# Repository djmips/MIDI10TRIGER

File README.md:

# MIDI10TRIGER
MIDI 2 eleven triggers with clock and reset

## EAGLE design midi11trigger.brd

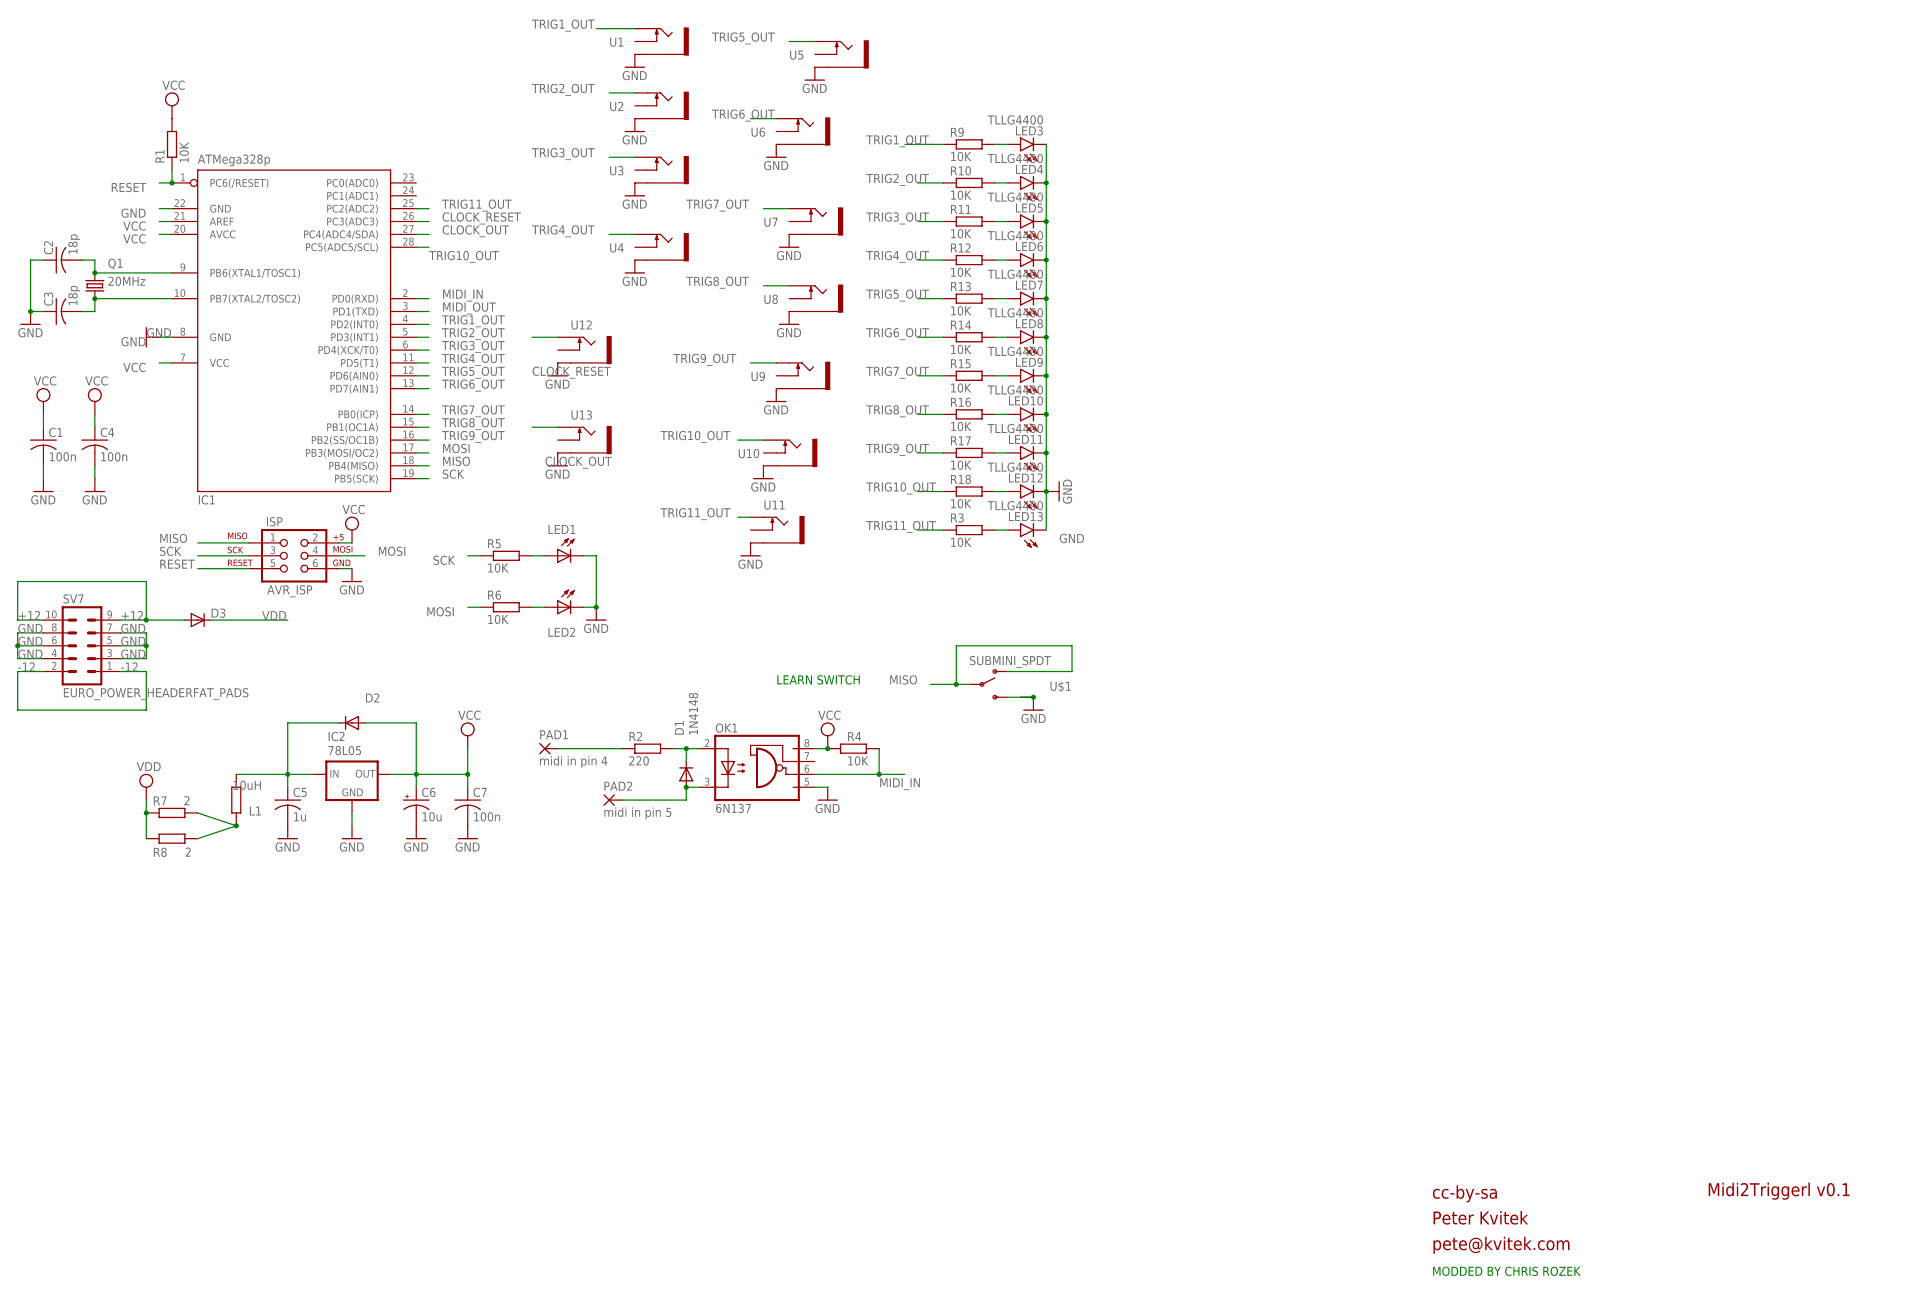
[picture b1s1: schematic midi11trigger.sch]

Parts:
C1, C4, C7: 100n; C025-025X050
C2, C3: 18p; C025-025X050
C5: 1u; C025-025X050
C6: 10u; E2,5-5
D1: 1N4148; DO35-7
D2, D3: SMALL_DIODEDO35-7; DO35-7
IC1: ATMega328p; DIL28-3
IC2: 78L05; 78LXX
ISP: AVR_ISP; 2X3
L1: 10uH; VERTICAL_RESISTOR
LED1, LED2: LED3MM
LED3, LED4, LED5, LED6, LED7, LED8, LED9, LED10, LED11, LED12, LED13: TLLG4400; LED3MM
OK1: 6N137; DIL08
PAD1: midi in pin 4; 2,54/1,1
PAD2: midi in pin 5; 2,54/1,1
Q1: 20MHz; HC49U-V
R1, R3, R4, R5, R6, R9, R10, R11, R12, R13, R14, R15, R16, R17, R18: 10K; VERTICAL_RESISTOR
R2: 220; VERTICAL_RESISTOR
R7, R8: 2; VERTICAL_RESISTOR
SV7: EURO_POWER_HEADERFAT_PADS; EURO_PWR_HEADER_FAT
U1, U2, U3, U4, U5, U6, U7, U8, U9, U10, U11, U12, U13: THONKICONNNEW; WQP-PJ301M-12_JACK
U$1: SUBMINI_SPDT; SUBMINI_TOGGLE

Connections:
+12: D3.A, SV7.9, SV7.10
-12: SV7.1, SV7.2
CLOCK_OUT: IC1.27 (PC4(ADC4/SDA)), U13.P$1_TIP (TIP)
CLOCK_RESET: IC1.26 (PC3(ADC3)), U12.P$1_TIP (TIP)
GND: C1.2, C2.1, C3.1, C4.2, C5.2, C6.-, C7.2, IC1.8 (GND), IC1.22 (GND), IC2.GND, ISP.6, LED1.K (C), LED2.K (C), LED3.K (C), LED4.K (C), LED5.K (C), LED6.K (C), LED7.K (C), LED8.K (C), LED9.K (C), LED10.K (C), LED11.K (C), LED12.K (C), LED13.K (C), OK1.5 (GND), SV7.3, SV7.4, SV7.5, SV7.6, SV7.7, SV7.8, U1.P$3_SLEEVE (SLEEVE), U2.P$3_SLEEVE (SLEEVE), U3.P$3_SLEEVE (SLEEVE), U4.P$3_SLEEVE (SLEEVE), U5.P$3_SLEEVE (SLEEVE), U6.P$3_SLEEVE (SLEEVE), U7.P$3_SLEEVE (SLEEVE), U8.P$3_SLEEVE (SLEEVE), U9.P$3_SLEEVE (SLEEVE), U10.P$3_SLEEVE (SLEEVE), U11.P$3_SLEEVE (SLEEVE), U12.P$3_SLEEVE (SLEEVE), U13.P$3_SLEEVE (SLEEVE), U$1.3 (S)
MIDI_IN: IC1.2 (PD0(RXD)), OK1.6 (VO), R4.2
MIDI_OUT: IC1.3 (PD1(TXD))
MISO: IC1.18 (PB4(MISO)), ISP.1, U$1.1 (O), U$1.COM (COMMON)
MOSI: IC1.17 (PB3(MOSI/OC2)), ISP.4, R6.1
unnamed: L1.1, R7.2, R8.2
unnamed: D1.C, OK1.2 (A), R2.2
unnamed: LED13.A, R3.2
unnamed: LED1.A, R5.2
unnamed: LED2.A, R6.2
unnamed: LED3.A, R9.2
unnamed: LED4.A, R10.2
unnamed: LED5.A, R11.2
unnamed: LED6.A, R12.2
unnamed: LED7.A, R13.2
unnamed: LED8.A, R14.2
unnamed: LED9.A, R15.2
unnamed: LED10.A, R16.2
unnamed: LED11.A, R17.2
unnamed: LED12.A, R18.2
unnamed: PAD1.1, R2.1
unnamed: D1.A, OK1.3 (C), PAD2.1
unnamed: C3.2, IC1.10 (PB7(XTAL2/TOSC2)), Q1.1
unnamed: C2.2, IC1.9 (PB6(XTAL1/TOSC1)), Q1.2
RESET: IC1.1 (PC6(/RESET)), ISP.5, R1.1
SCK: IC1.19 (PB5(SCK)), ISP.3, R5.1
TRIG1_OUT: IC1.4 (PD2(INT0)), R9.1, U1.P$1_TIP (TIP)
TRIG2_OUT: IC1.5 (PD3(INT1)), R10.1, U2.P$1_TIP (TIP)
TRIG3_OUT: IC1.6 (PD4(XCK/T0)), R11.1, U3.P$1_TIP (TIP)
TRIG4_OUT: IC1.11 (PD5(T1)), R12.1, U4.P$1_TIP (TIP)
TRIG5_OUT: IC1.12 (PD6(AIN0)), R13.1, U5.P$1_TIP (TIP)
TRIG6_OUT: IC1.13 (PD7(AIN1)), R14.1, U6.P$1_TIP (TIP)
TRIG7_OUT: IC1.14 (PB0(ICP)), R15.1, U7.P$1_TIP (TIP)
TRIG8_OUT: IC1.15 (PB1(OC1A)), R16.1, U8.P$1_TIP (TIP)
TRIG9_OUT: IC1.16 (PB2(SS/OC1B)), R17.1, U9.P$1_TIP (TIP)
TRIG10_OUT: IC1.28 (PC5(ADC5/SCL)), R18.1, U10.P$1_TIP (TIP)
TRIG11_OUT: IC1.25 (PC2(ADC2)), R3.1, U11.P$1_TIP (TIP)
VCC: C1.1, C4.1, C6.+, C7.1, D2.A, IC1.7 (VCC), IC1.20 (AVCC), IC1.21 (AREF), IC2.OUT, ISP.2, OK1.8 (VCC), R1.2, R4.1
VDD: D3.C, R7.1, R8.1
VREG_IN: C5.1, D2.C, IC2.IN, L1.2

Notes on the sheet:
cc-by-sa
Peter Kvitek
pete@kvitek.com
Midi2Triggerl v0.1
LEARN SWITCH
MODDED BY CHRIS ROZEK

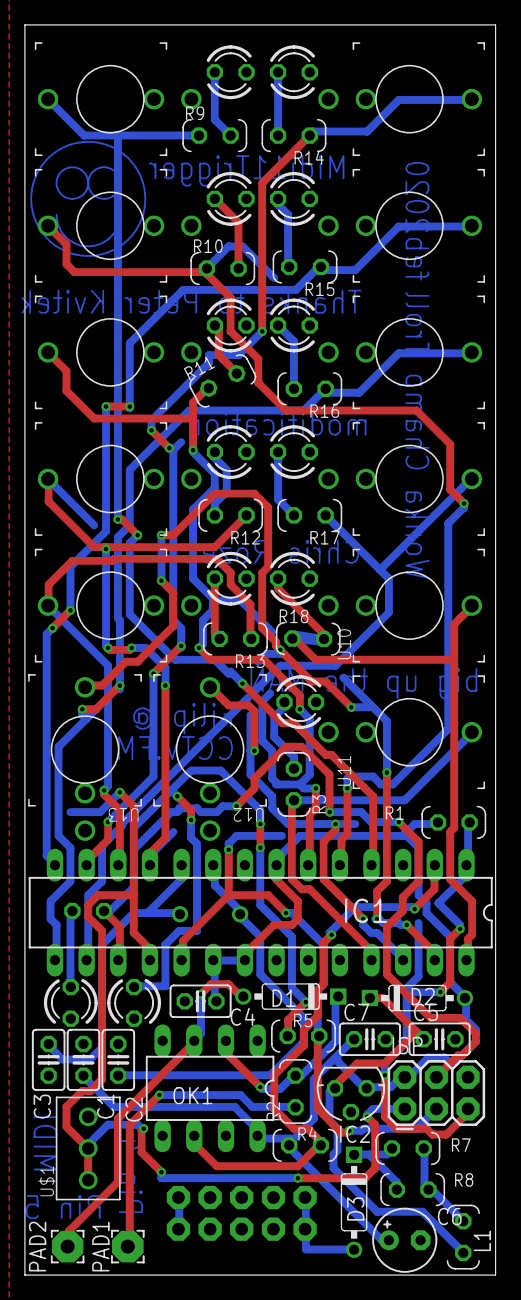
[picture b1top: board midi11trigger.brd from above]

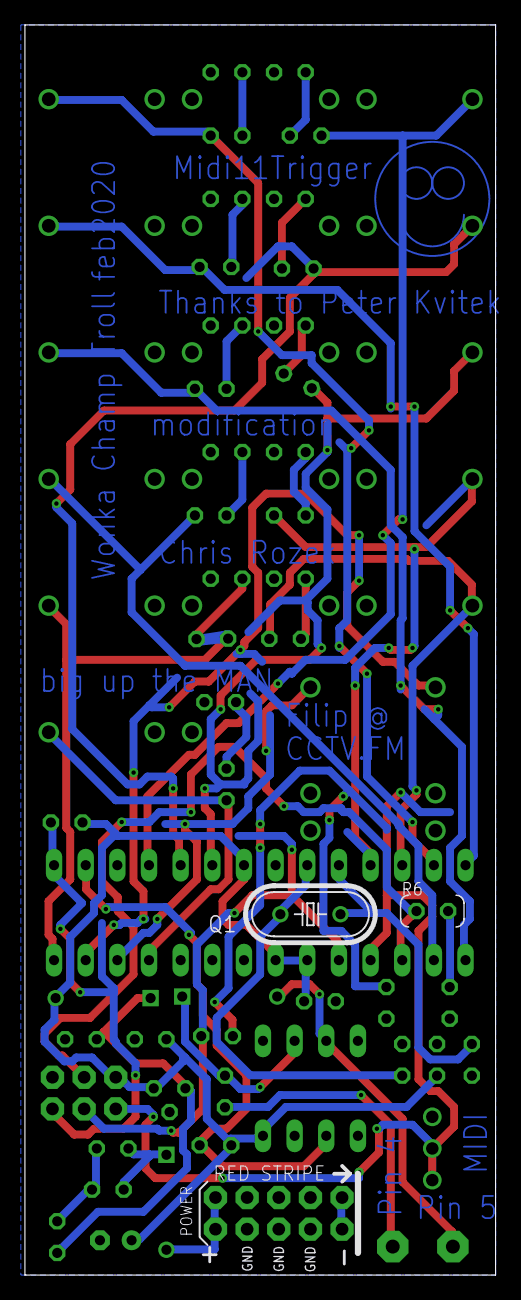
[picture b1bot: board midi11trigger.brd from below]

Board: 2 copper layers, 37.8 x 100.3 mm, 64 parts (3 on the bottom side), 43 nets.

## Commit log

2020-02-05 Add files via upload
    reworked
2020-03-07 Add the source with Mutable pinchnettes avrlib
2020-03-07 Found different and probably correct version of the lib floating around in Peter Kvitek github
